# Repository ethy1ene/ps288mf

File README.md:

# PS288MF

A simple Arduino-based PS/2 to PC-8801F/M keyboard adapter.

PC-8801FH以降用のPS2キーボードアダプター 

Need PS2keyAdvanced library.

# Default pinout

|PS/2 keyboard|Arduino|PC-8801 host|
|:-----------:|:-----:| :---------:|
|+5v|+5v|+5v|
|   |D6|Rx|
|DATA|D4||
|CLK|D3||
|GND|GND|GND|

PC-88MA side pinout:

# Keymap

# Usage

Just buy a Arduino Nano, upload the codes, connect the cables as above. :)

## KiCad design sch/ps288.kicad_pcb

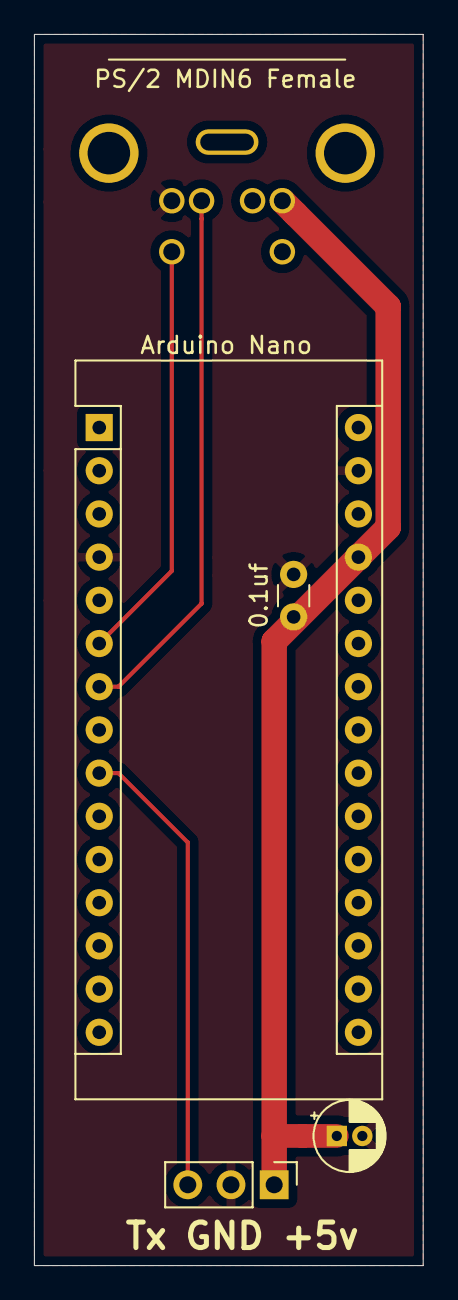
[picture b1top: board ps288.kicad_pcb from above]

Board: 2 copper layers, 22.9 x 72.4 mm, 5 parts (0 on the bottom side), 5 nets.

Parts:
0.1uf: C; C_Disc_D3.0mm_W1.6mm_P2.50mm
A1: Arduino_Nano_v3.x; Arduino_Nano
C1: CP1; CP_Radial_D4.0mm_P1.50mm
J1: Mini-DIN-6; mdin6
J2: Conn_01x03_Female; PinHeader_1x03_P2.54mm_Vertical

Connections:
+5V: 0.1uf.1, A1.27, C1.1, J1.4, J2.1
GND: 0.1uf.2, A1.4, A1.29, C1.2, J1.3, J2.2
unnamed: A1.6, J1.5
unnamed: A1.7, J1.1
unnamed: A1.9, J2.3

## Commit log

2019-07-11 Add files via upload
    v1.0beta
2019-07-11 Create LICENSE-WTFPL
2019-07-12 fix bugs
    fix some bugs , add more bugs.
2019-07-12 install ps2adv lib by yourself
2019-07-12 add default pinout.
2020-02-09 better timer and delay() value
2020-02-10 fix some bug.
2020-02-10 Add PCB files.
2022-10-30 Fix numpad keycode.
